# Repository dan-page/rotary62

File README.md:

# rotary62
ISO 65% Keyboard with Integrated Plate and Rotary Encoder

Includes:
- Case 
- Base
- PCB
- Silicone Sound Dampener
- Encoder Knob
- Rubber Feet

## Case
Machined out of 6063 Aluminium and finished in E-White

## Base
Machined out of 6063 Aluminium and anodised black.

## PCB
The PCB was designed to use common components from JLCPCB. Firmware is available from the [QMK Repo](https://github.com/qmk/qmk_firmware).

## Silicone Sound Dampener
This includes a 3D printable mould that can be filled with silicone to create a sound dampener for inside the case. After 3D printing the two parts of the mould need glueing together and the seam between the two parts making smooth through sanding and filler. 

## Encoder Knob
Machined out of Brass and polished.

## Rubber Feet
Cut from a strip of adhesive-backed 60SH Black Silicone and stuck to the recessed gaps on the base.

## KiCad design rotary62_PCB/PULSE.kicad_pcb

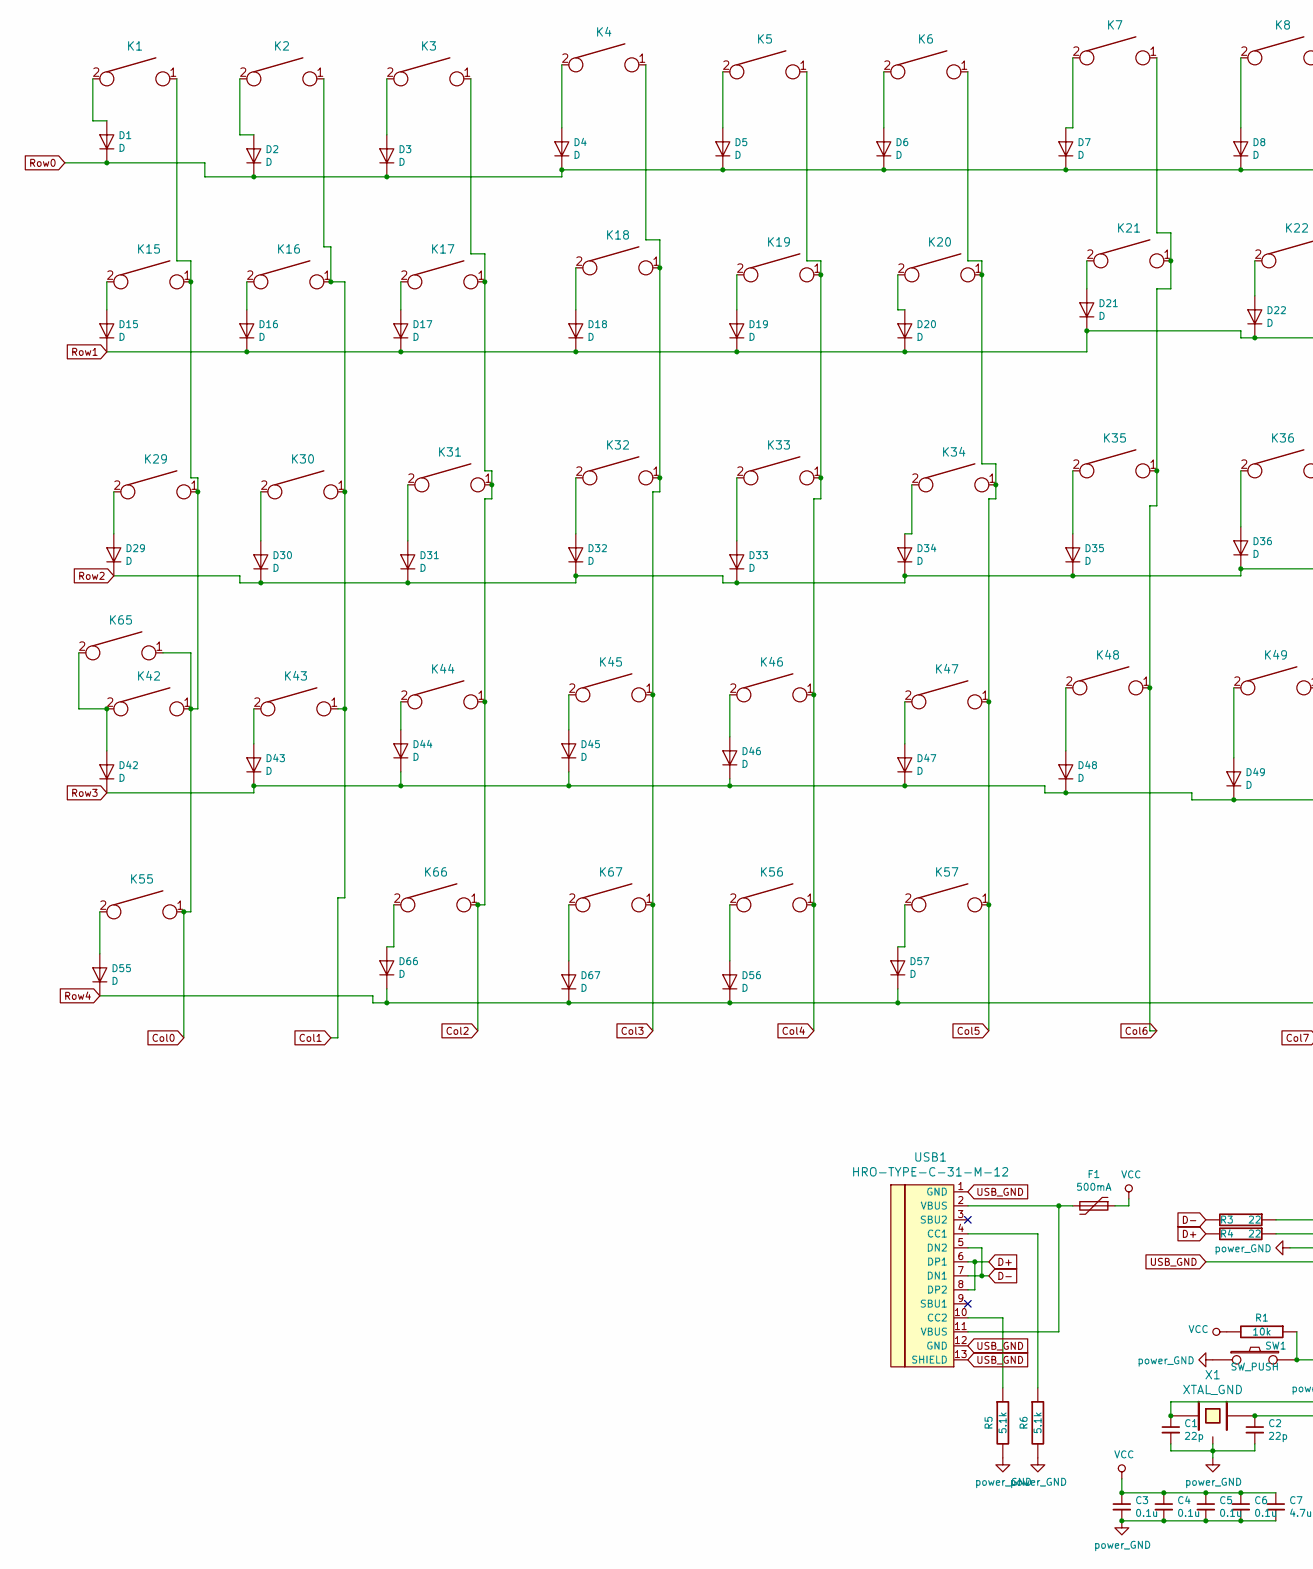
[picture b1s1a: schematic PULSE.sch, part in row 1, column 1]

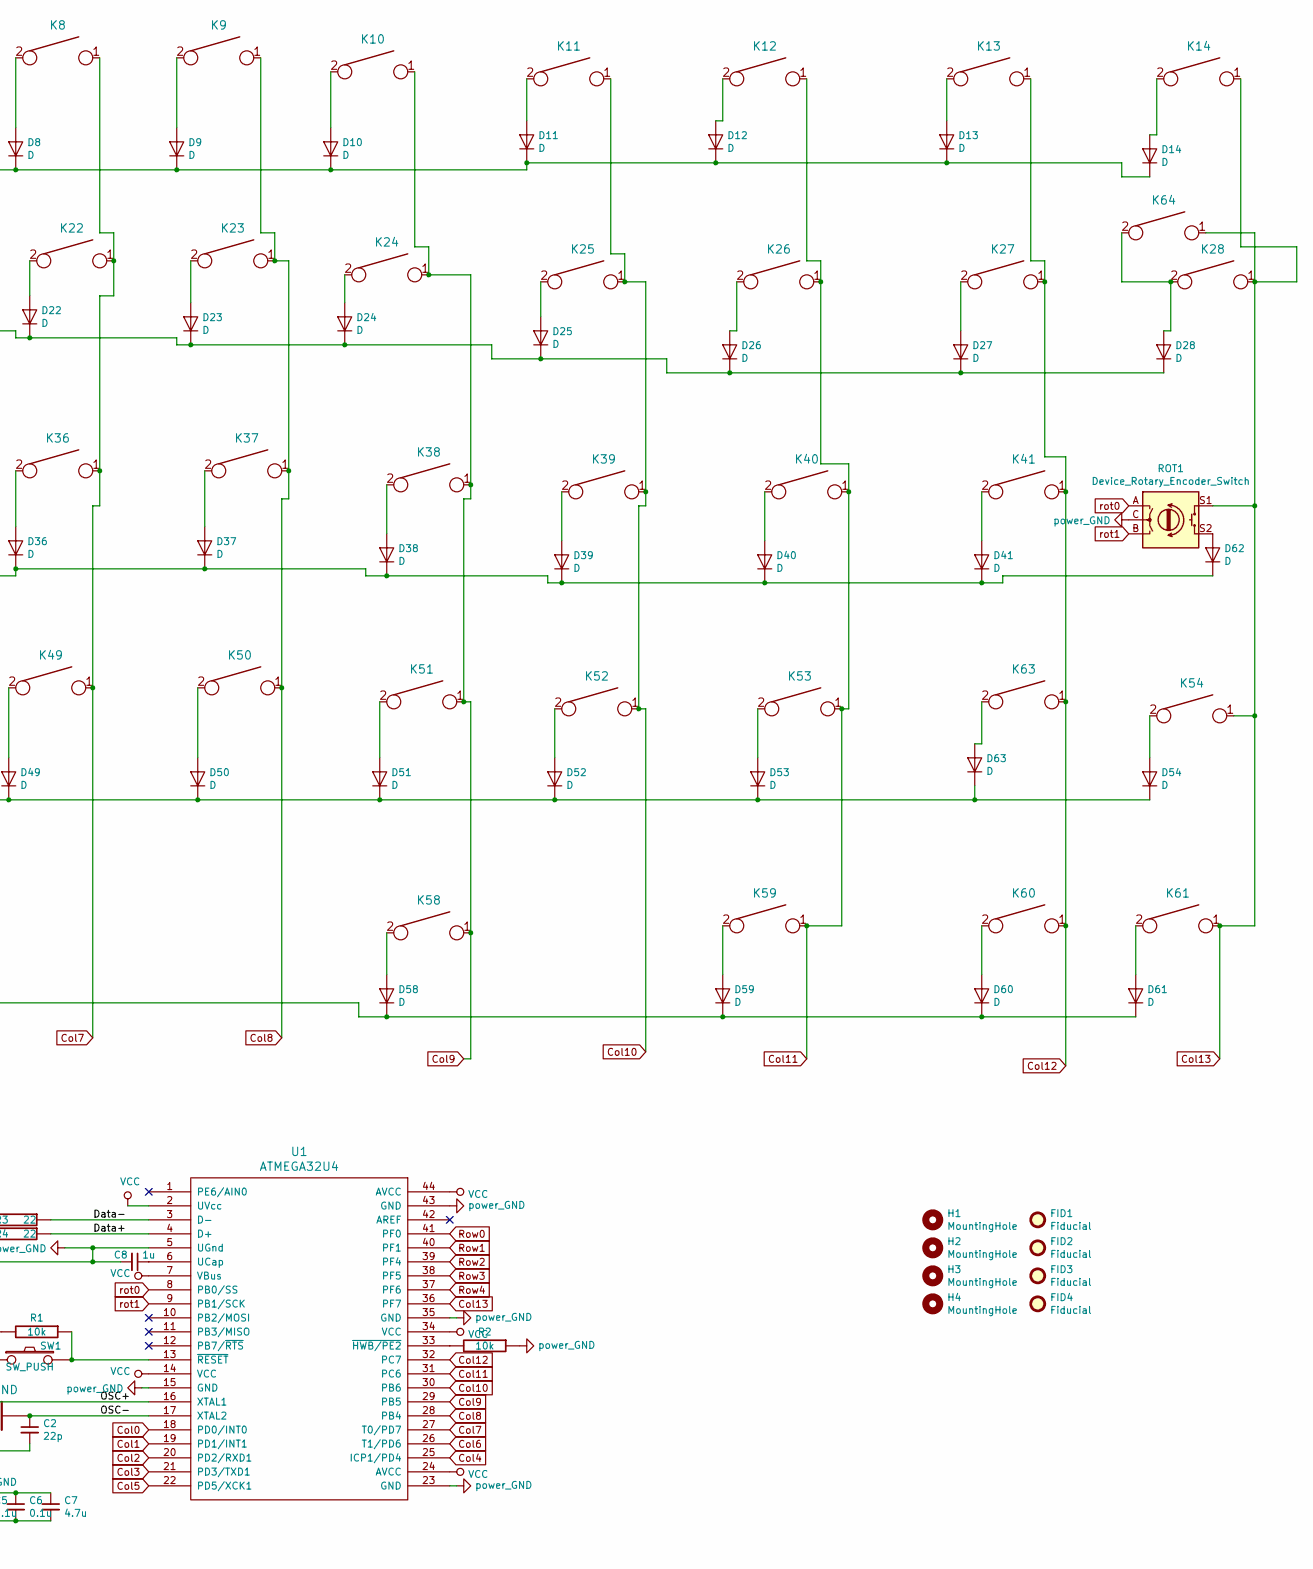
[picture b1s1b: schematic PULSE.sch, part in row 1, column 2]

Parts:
C1, C2: 22p; C_0805_HandSoldering
C3, C4, C5, C6: 0.1u; C_0805_HandSoldering
C7: 4.7u; C_0805_HandSoldering
C8: 1u; C_0805_HandSoldering
D1, D2, D3, D4, D5, D6, D7, D8, D9, D10, D11, D12, D13, D14, D15, D16, D17, D18, D19, D20, D21, D22, D23, D24, D25, D26, D27, D28, D29, D30, D31, D32, D33, D34, D35, D36, D37, D38, D39, D40, D41, D42, D43, D44, D45, D46, D47, D48, D49, D50, D51, D52, D53, D54, D55, D56, D57, D58, D59, D60, D61, D62, D63, D66, D67: D; D_SOD123_handD
F1: 500mA; C_1206_HandSoldering
FID1, FID2, FID3, FID4: Fiducial; Fiducial_1mm_Dia_2mm_Outer
H1, H2, H3, H4: MountingHole; MountingHole_3.5mm_Pad
K1, K2, K3, K4, K5, K6, K7, K8, K9, K10, K11, K12, K13, K16, K17, K18, K19, K20, K21, K22, K23, K24, K25, K26, K27, K30, K31, K32, K33, K34, K35, K36, K37, K38, K39, K40, K43, K44, K45, K46, K47, K48, K49, K50, K51, K52, K54, K59, K60, K61, K67: KEYSW; MXOnly-1U-Hotswap
K14: KEYSW; MXOnly-2U-Hotswap
K15, K55, K56, K58, K63: KEYSW; MXOnly-1.5U-Hotswap
K28: KEYSW; ISO_Hotswap
K29: KEYSW; MXOnly-1.75U-Hotswap
K41: KEYSW; 1U 2 up
K42: KEYSW; 2.25U 2 up
K53: KEYSW; MXOnly-2.25U-Hotswap
K57: KEYSW; MXOnly-7U-Hotswap
K64: KEYSW; 2.25u 1u down
K65: KEYSW; MXOnly-1.25U-Hotswap
K66: KEYSW; 1U 1 down
R1, R2: 10k; R_0805_HandSoldering
R3, R4: 22; R_0805_HandSoldering
R5, R6: 5.1k; R_0805_HandSoldering
ROT1: Device_Rotary_Encoder_Switch; RotaryEncoder_Alps_EC11E-Switch_Vertical_H20mm
SW1: SW_PUSH; SW_SPST_TL3342
U1: ATMEGA32U4; TQFP-44_10x10mm_Pitch0.8mm
USB1: HRO-TYPE-C-31-M-12; HRO-TYPE-C-31-M-12-HandSoldering
X1: XTAL_GND; FA-238

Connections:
/Data+: R4.1, U1.4 (D+)
/Data-: R3.1, U1.3 (D-)
/OSC+: C1.1, U1.16 (XTAL1), X1.1
/OSC-: C2.1, U1.17 (XTAL2), X1.2
Col0: K1.1, K15.1, K29.1, K42.1, K55.1, K65.1, U1.18 (PD0/INT0)
Col1: K2.1, K16.1, K30.1, K43.1, U1.19 (PD1/INT1)
Col2: K3.1, K17.1, K31.1, K44.1, K66.1, U1.20 (PD2/RXD1)
Col3: K4.1, K18.1, K32.1, K45.1, K67.1, U1.21 (PD3/TXD1)
Col4: K5.1, K19.1, K33.1, K46.1, K56.1, U1.25 (ICP1/PD4)
Col5: K6.1, K20.1, K34.1, K47.1, K57.1, U1.22 (PD5/XCK1)
Col6: K7.1, K21.1, K35.1, K48.1, U1.26 (T1/PD6)
Col7: K8.1, K22.1, K36.1, K49.1, U1.27 (T0/PD7)
Col8: K9.1, K23.1, K37.1, K50.1, U1.28 (PB4)
Col9: K10.1, K24.1, K38.1, K51.1, K58.1, U1.29 (PB5)
Col10: K11.1, K25.1, K39.1, K52.1, U1.30 (PB6)
Col11: K12.1, K26.1, K40.1, K53.1, K59.1, U1.31 (PC6)
Col12: K13.1, K27.1, K41.1, K60.1, K63.1, U1.32 (PC7)
Col13: K14.1, K28.1, K54.1, K61.1, K64.1, ROT1.S1, U1.36 (PF7)
D+: R4.2, USB1.6 (DP1), USB1.8 (DP2)
D-: R3.2, USB1.5 (DN2), USB1.7 (DN1)
unnamed: C8.1, U1.6 (UCap)
unnamed: D1.2 (A), K1.2
unnamed: D2.2 (A), K2.2
unnamed: D3.2 (A), K3.2
unnamed: D4.2 (A), K4.2
unnamed: D5.2 (A), K5.2
unnamed: D6.2 (A), K6.2
unnamed: D7.2 (A), K7.2
unnamed: D8.2 (A), K8.2
unnamed: D9.2 (A), K9.2
unnamed: D10.2 (A), K10.2
unnamed: D11.2 (A), K11.2
unnamed: D12.2 (A), K12.2
unnamed: D13.2 (A), K13.2
unnamed: D14.2 (A), K14.2
unnamed: D15.2 (A), K15.2
unnamed: D16.2 (A), K16.2
unnamed: D17.2 (A), K17.2
unnamed: D18.2 (A), K18.2
unnamed: D19.2 (A), K19.2
unnamed: D20.2 (A), K20.2
unnamed: D21.2 (A), K21.2
unnamed: D22.2 (A), K22.2
unnamed: D23.2 (A), K23.2
unnamed: D24.2 (A), K24.2
unnamed: D25.2 (A), K25.2
unnamed: D26.2 (A), K26.2
unnamed: D27.2 (A), K27.2
unnamed: D28.2 (A), K28.2, K64.2
unnamed: D29.2 (A), K29.2
unnamed: D30.2 (A), K30.2
unnamed: D31.2 (A), K31.2
unnamed: D32.2 (A), K32.2
unnamed: D33.2 (A), K33.2
unnamed: D34.2 (A), K34.2
unnamed: D35.2 (A), K35.2
unnamed: D36.2 (A), K36.2
unnamed: D37.2 (A), K37.2
unnamed: D38.2 (A), K38.2
unnamed: D39.2 (A), K39.2
unnamed: D40.2 (A), K40.2
unnamed: D41.2 (A), K41.2
unnamed: D42.2 (A), K42.2, K65.2
unnamed: D43.2 (A), K43.2
unnamed: D44.2 (A), K44.2
unnamed: D45.2 (A), K45.2
unnamed: D46.2 (A), K46.2
unnamed: D47.2 (A), K47.2
unnamed: D48.2 (A), K48.2
unnamed: D49.2 (A), K49.2
unnamed: D50.2 (A), K50.2
unnamed: D51.2 (A), K51.2
unnamed: D52.2 (A), K52.2
unnamed: D53.2 (A), K53.2
unnamed: D54.2 (A), K54.2
unnamed: D55.2 (A), K55.2
unnamed: D56.2 (A), K56.2
unnamed: D57.2 (A), K57.2
unnamed: D58.2 (A), K58.2
unnamed: D59.2 (A), K59.2
unnamed: D60.2 (A), K60.2
unnamed: D61.2 (A), K61.2
unnamed: D62.2 (A), ROT1.S2
unnamed: D63.2 (A), K63.2
unnamed: D66.2 (A), K66.2
unnamed: D67.2 (A), K67.2
unnamed: F1.2, USB1.2 (VBUS), USB1.11 (VBUS)
unnamed: R1.1, SW1.2, U1.13 (~RESET)
unnamed: R2.2, U1.33 (~HWB/PE2)
unnamed: R5.1, USB1.10 (CC2)
unnamed: R6.1, USB1.4 (CC1)
Row0: D1.1 (K), D2.1 (K), D3.1 (K), D4.1 (K), D5.1 (K), D6.1 (K), D7.1 (K), D8.1 (K), D9.1 (K), D10.1 (K), D11.1 (K), D12.1 (K), D13.1 (K), D14.1 (K), U1.41 (PF0)
Row1: D15.1 (K), D16.1 (K), D17.1 (K), D18.1 (K), D19.1 (K), D20.1 (K), D21.1 (K), D22.1 (K), D23.1 (K), D24.1 (K), D25.1 (K), D26.1 (K), D27.1 (K), D28.1 (K), U1.40 (PF1)
Row2: D29.1 (K), D30.1 (K), D31.1 (K), D32.1 (K), D33.1 (K), D34.1 (K), D35.1 (K), D36.1 (K), D37.1 (K), D38.1 (K), D39.1 (K), D40.1 (K), D41.1 (K), D62.1 (K), U1.39 (PF4)
Row3: D42.1 (K), D43.1 (K), D44.1 (K), D45.1 (K), D46.1 (K), D47.1 (K), D48.1 (K), D49.1 (K), D50.1 (K), D51.1 (K), D52.1 (K), D53.1 (K), D54.1 (K), D63.1 (K), U1.38 (PF5)
Row4: D55.1 (K), D56.1 (K), D57.1 (K), D58.1 (K), D59.1 (K), D60.1 (K), D61.1 (K), D66.1 (K), D67.1 (K), U1.37 (PF6)
USB_GND: C1.2, C2.2, C3.2, C4.2, C5.2, C6.2, C7.2, C8.2, R2.1, R5.2, R6.2, ROT1.C, SW1.1, U1.5 (UGnd), U1.15 (GND), U1.23 (GND), U1.35 (GND), U1.43 (GND), USB1.1 (GND), USB1.12 (GND), USB1.13 (SHIELD), X1.3
VCC: C3.1, C4.1, C5.1, C6.1, C7.1, F1.1, R1.2, U1.2 (UVcc), U1.7 (VBus), U1.14 (VCC), U1.24 (AVCC), U1.34 (VCC), U1.44 (AVCC)
rot0: ROT1.A, U1.8 (PB0/SS)
rot1: ROT1.B, U1.9 (PB1/SCK)

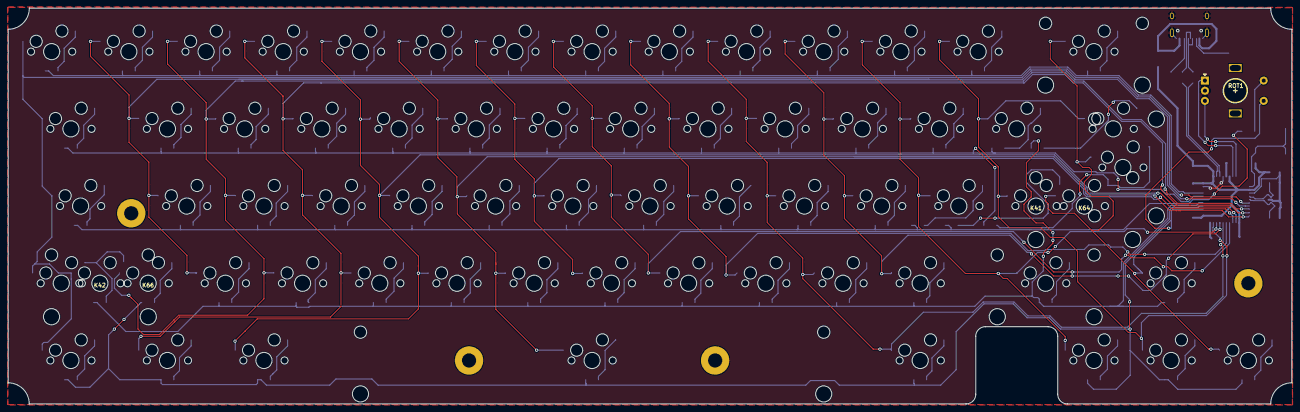
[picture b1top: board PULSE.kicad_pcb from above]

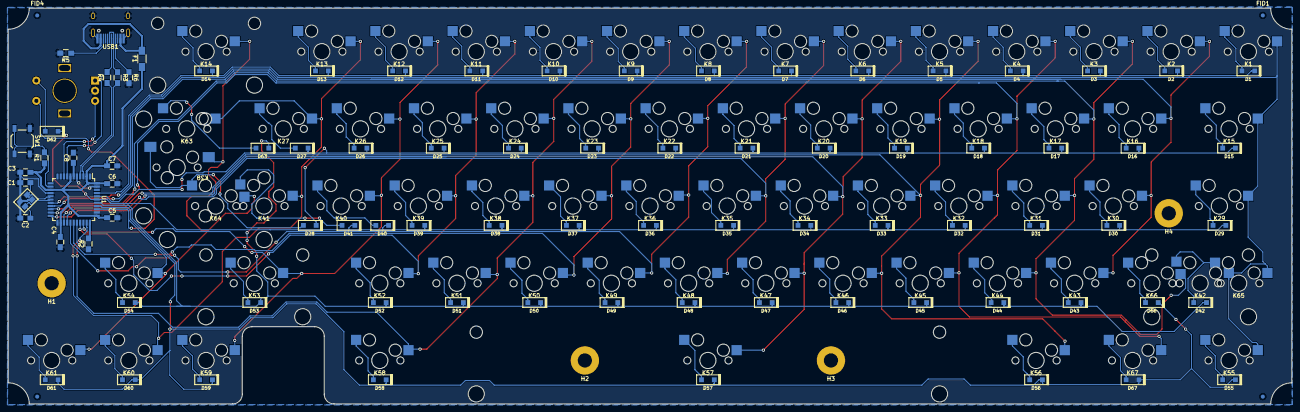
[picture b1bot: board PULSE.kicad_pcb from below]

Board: 2 copper layers, 316.7 x 97.6 mm, 159 parts (92 on the bottom side), 100 nets.

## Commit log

2024-03-25 Added PCB files for the Rotary62
2024-03-25 Create LICENSE
2024-03-25 Case files and drawings added
2024-03-25 added image
2024-03-25 Added 3D printing files for sound dampener
